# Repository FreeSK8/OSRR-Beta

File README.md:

# OSRR-Beta

## LEGACY OSRR Beta Project - retired 2019 - See FreeSK8 Remote Project for continued development. 

OSRR- Open Source Racing Remote, which serves as an open spec reference design for a robust remote control device, for use with VESC/Unity based PEVs. 

### Authors & Contributors:
Andrew Dresner

Renee Love

For information on setup & usage, please see the Wiki: 

https://github.com/FreeSK8/OSRR/wiki

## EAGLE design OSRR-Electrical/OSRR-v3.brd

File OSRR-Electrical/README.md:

# OSRR Electrical

EagleCAD 9.3.2

TODO: EagleCAD Libraries, BOM

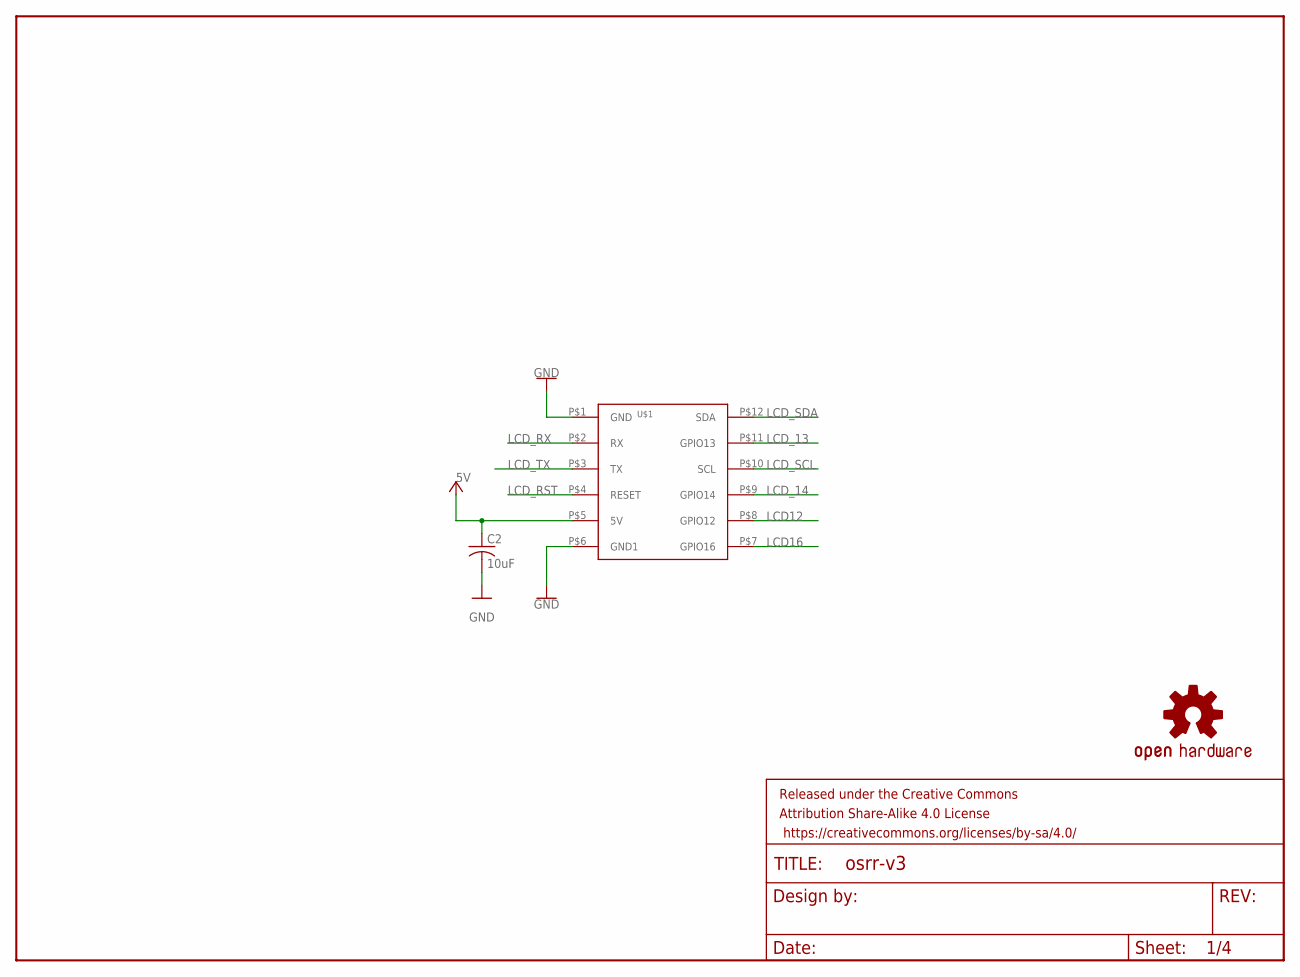
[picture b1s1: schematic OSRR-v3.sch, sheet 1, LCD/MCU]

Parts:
C2: 10uF; C0603
FRAME1: FRAME-LETTER; CREATIVE_COMMONS
LOGO1: OSHW-LOGOS; OSHW-LOGO-S
U$1: IOD-09; IOD-9TH

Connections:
5V: C2.1, U$1.P$5 (5V); also elsewhere on the board
GND: C2.2, U$1.P$1 (GND), U$1.P$6 (GND1); also elsewhere on the board
LCD12: U$1.P$8 (GPIO12)
LCD16: U$1.P$7 (GPIO16)
LCD_13: U$1.P$11 (GPIO13)
LCD_14: U$1.P$9 (GPIO14)
LCD_RST: U$1.P$4 (RESET)
LCD_RX: U$1.P$2 (RX); also elsewhere on the board
LCD_SCL: U$1.P$10 (SCL); also elsewhere on the board
LCD_SDA: U$1.P$12 (SDA); also elsewhere on the board
LCD_TX: U$1.P$3 (TX); also elsewhere on the board

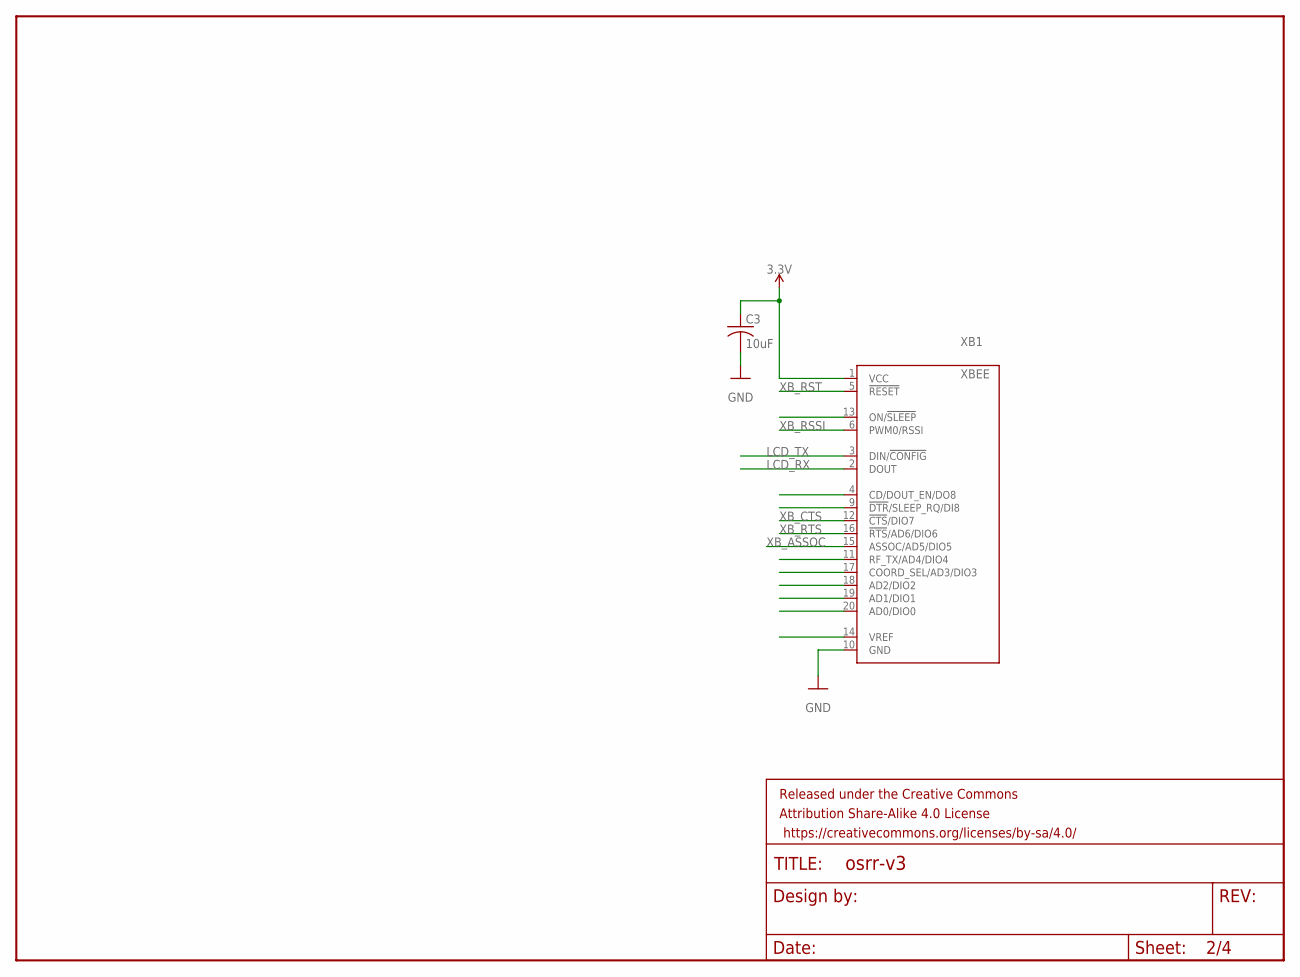
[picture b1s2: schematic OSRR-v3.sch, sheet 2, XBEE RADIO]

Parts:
C3: 10uF; C0603
FRAME2: FRAME-LETTER; CREATIVE_COMMONS
XB1: XBEE

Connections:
3.3V: C3.1, XB1.1 (VCC); also elsewhere on the board
GND: C3.2, XB1.10 (GND); also elsewhere on the board
LCD_RX: XB1.2 (DOUT); also elsewhere on the board
LCD_TX: XB1.3 (DIN/!CONFIG); also elsewhere on the board
XB_ASSOC: XB1.15 (ASSOC/AD5/DIO5)
XB_CTS: XB1.12 (!CTS!/DIO7)
XB_RSSI: XB1.6 (PWM0/RSSI); also elsewhere on the board
XB_RST: XB1.5 (!RESET)
XB_RTS: XB1.16 (!RTS!/AD6/DIO6)

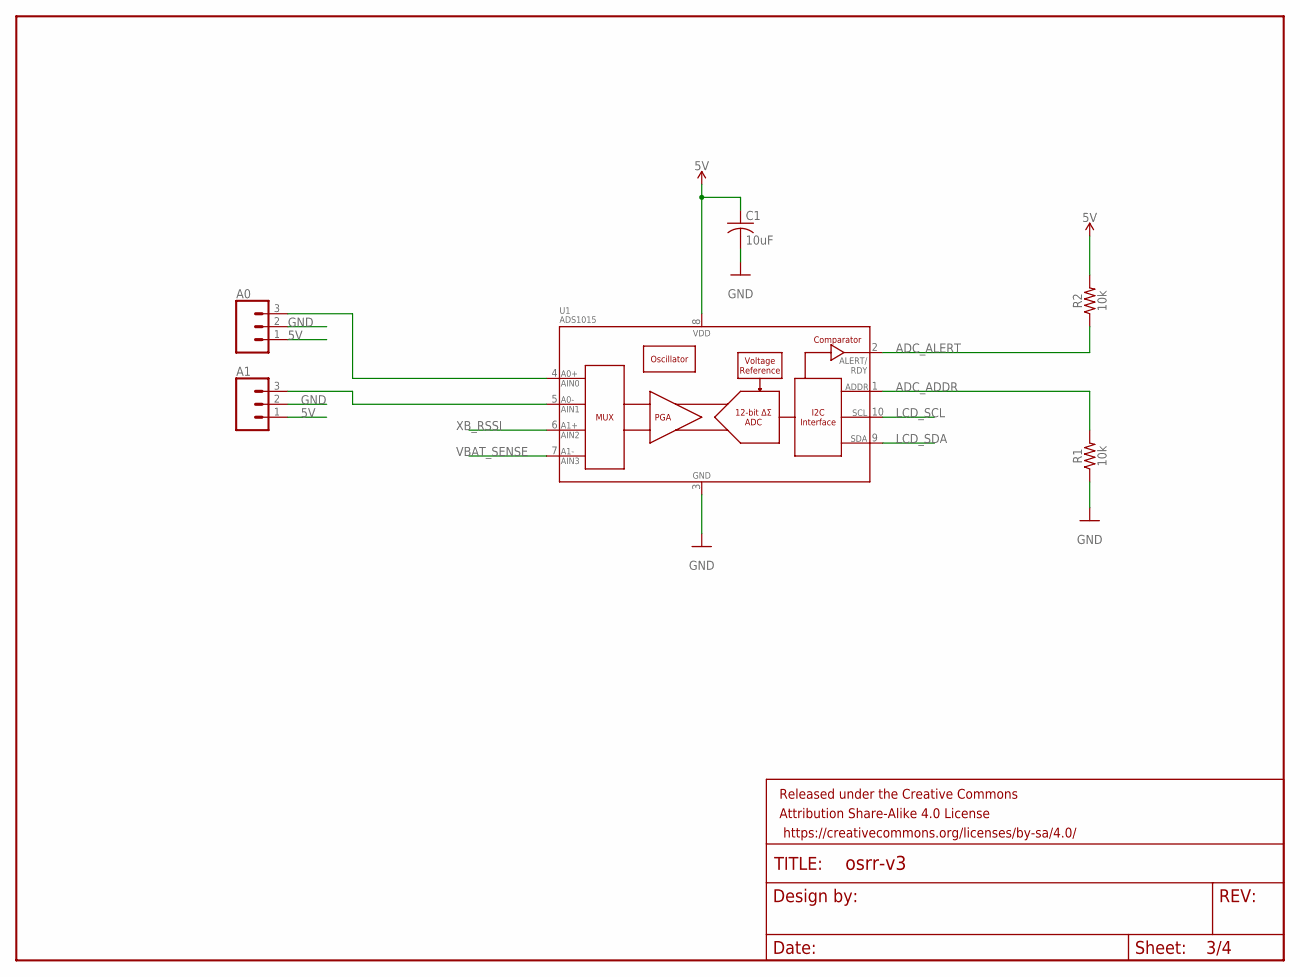
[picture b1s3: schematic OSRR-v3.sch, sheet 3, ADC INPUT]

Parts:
A0, A1: CONN_03JST-PTH-VERT; JST-3-PTH-VERT
C1: 10uF; C0603
FRAME3: FRAME-LETTER; CREATIVE_COMMONS
R1, R2: 10k; 0603
U1: ADS1015; MSOP10

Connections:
5V: A0.1, A1.1, C1.1, R2.2, U1.8 (VDD); also elsewhere on the board
ADC_ADDR: R1.2, U1.1 (ADDR)
ADC_ALERT: R2.1, U1.2 (ALERT/RDY)
GND: A0.2, A1.2, C1.2, R1.1, U1.3 (VSS); also elsewhere on the board
LCD_SCL: U1.10 (SCL); also elsewhere on the board
LCD_SDA: U1.9 (SDA); also elsewhere on the board
unnamed: A0.3, U1.4 (AIN0)
unnamed: A1.3, U1.5 (AIN1)
VBAT_SENSE: U1.7 (AIN3); also elsewhere on the board
XB_RSSI: U1.6 (AIN2); also elsewhere on the board

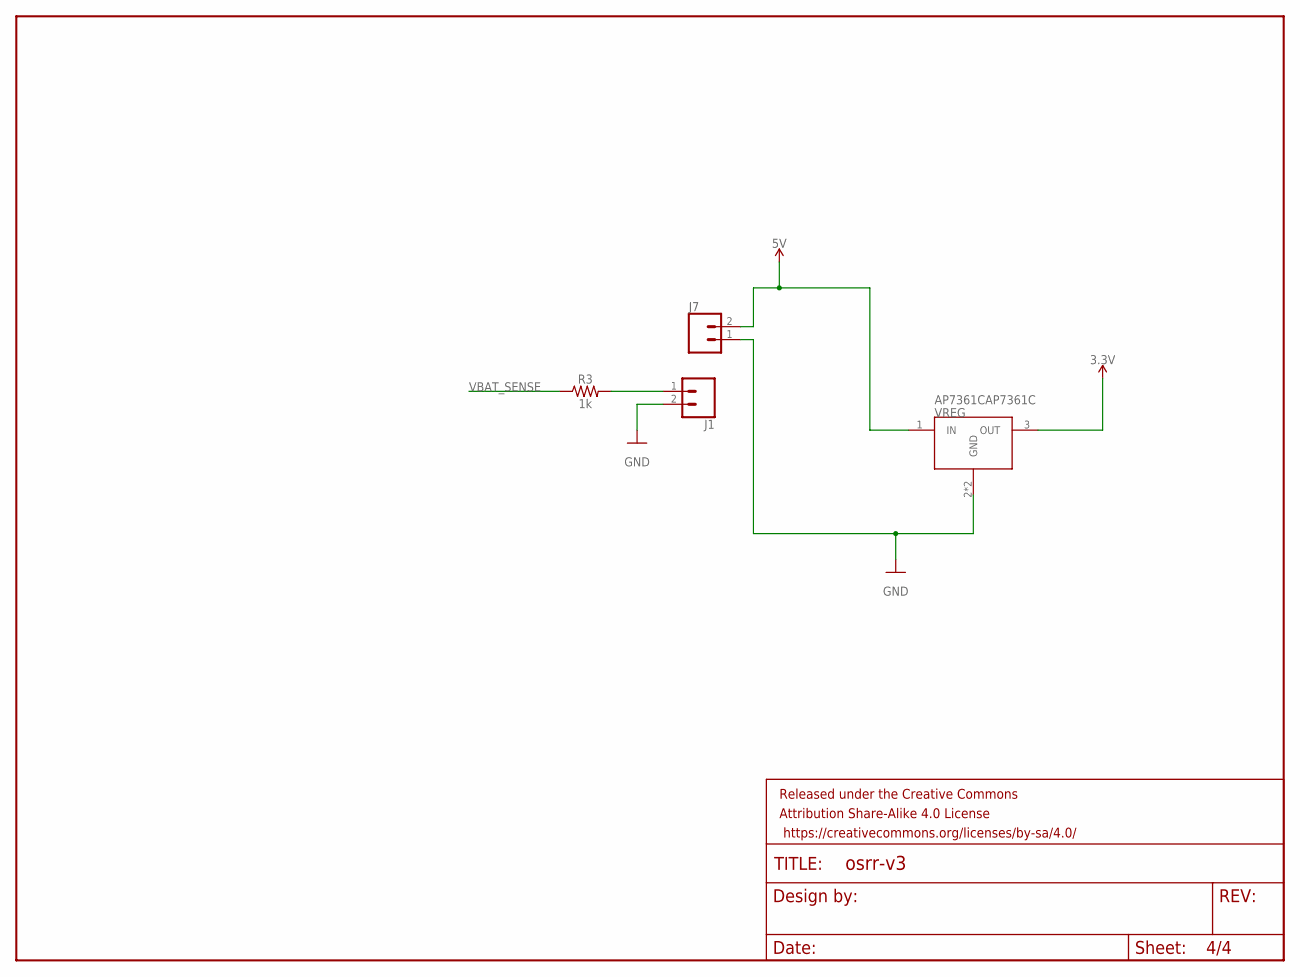
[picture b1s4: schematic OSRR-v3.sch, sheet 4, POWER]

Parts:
FRAME4: FRAME-LETTER; CREATIVE_COMMONS
J1: CONN_02; 1X02
J7: CONN_02-JST-2-PTH-NO_SILK; JST-2-PTH-NS
R3: 1k; 0603
VREG: AP7361CAP7361C; SOT230P700X180-4

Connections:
3.3V: VREG.3 (OUT); also elsewhere on the board
5V: J7.2, VREG.1 (IN); also elsewhere on the board
GND: J1.2, J7.1, VREG.2 (GND), VREG.4 (GND); also elsewhere on the board
unnamed: J1.1, R3.2
VBAT_SENSE: R3.1; also elsewhere on the board

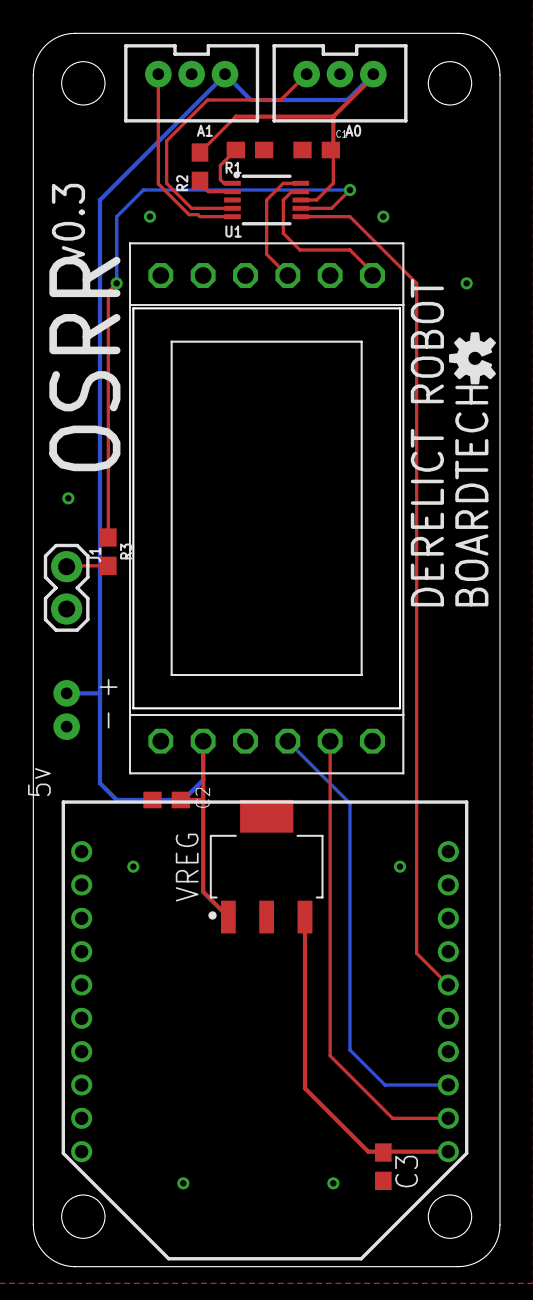
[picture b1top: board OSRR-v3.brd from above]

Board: 2 copper layers, 27.9 x 73.9 mm, 19 parts (0 on the bottom side), 14 nets.

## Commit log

2019-06-21 Initial Firmware Commit
2019-06-21 Reorg, initial electrical & mechanical push
2019-06-24 Updated to STL export. rev2 HMP model grip enclosure.
2019-06-25 Initial HHG model upload.
2019-07-28 Added metric option, odometer fix
2019-07-28 Enable remote battery monitor & display
2019-07-28 Battery Monitor updates
2019-07-31 Remote Battery Monitor Updates
2019-07-31 Remote Battery Monitoring Updates
2019-07-31 Added more blinkies, format linting
2019-08-11 Enclosure STL updates
2019-08-11 The Bruce update - added leash hardpoint
2019-08-13 Config.h creation, user modifiable parameters moved.
2019-08-13 Enclosure updates, HHG display port adj
2019-08-14 Added Bruce Fusion link.
2019-08-16 Bruce topshell adjustment
2019-08-24 HHG updates for leash hole
2019-09-02 Bruce updates
2019-09-02 Bruce Update
2019-09-02 HMP updates
2019-09-10 Added Xbee S2C Remote/Receiver Profiles
2019-10-08 Timer based throttle update
    change the throttle update routine to be trigered by a timer rather than relying on delay
2019-11-17 Added WiFiAP Config mode.
2019-11-17 changes to show logo at boot
2019-11-18 Cleanup.
2019-11-18 Remove old delay, fix.
2019-11-18 Update display.h
    rotate boot logo to better suit some remote models
2019-11-20 Full contact PR testing. Be safe out there, ferda.
    Added CRC check on EEPROM, loading of existing configuration values to webapp, included cell count field for color coded voltage display.
2019-11-22 added fonts files
    added unmodified fonts files from the VESC wand project at https://github.com/vedderb/vesc_wand
2019-11-23 added functions for colour handeling
    testing simpler RGB to 565Color function.
    Added functions for getting single colours from 565Color.
    Added function for mapping colours.
2019-11-23 added function to show char
    added function to write a single char to the display in any "wand format" font
2019-11-23 tidy
    add coment
2019-11-23 added "printf" function
    added function for printing strings in any font
2019-11-23 included example print
    example printf that can be comented in on boot screen to see new fonts
2019-11-23 Seperating Telemetry behaviour from feedback.
    the goal of this is to seperate telemetry functions from the display functions.
    This means that recieveing telemetry is no longer dependant on showing the "home screen" and the "home screen" can be updated without recieveing new telemetry data.
    This alows for future altering of whats being displayed whilst lowering the risk of affecting remote operation
2019-11-23 fix duplicate line
    fixing a quick error from last commit
2019-11-26 Fix for more acurate telemetry with carying drive configurations.
    Added a configurable for the number of ESC's alowing for acurate telemetry for single drive, dual drive and 4WD configurations.

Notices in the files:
parts and their libraries:
SparkFun-Aesthetics: Licensing: Creative Commons ShareAlike 4.0 International - https://creativecommons.org/licenses/by-sa/4.0
SparkFun-Aesthetics: Released under the Creative Commons Attribution Share-Alike 4.0 License
SparkFun-Aesthetics: https://creativecommons.org/licenses/by-sa/4.0
